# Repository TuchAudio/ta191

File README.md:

# ta191
Low Noise, improved Moving-Coil Phono Pre-Amp

## Purpose
An optional _previous_ stage for **MM Phono preamps** like [TuchAudio 101b](../../../ta101b), allowing the use of **Moving Coil** cartridges. _With suitable wiring_ it could be used with other preamps as well, like the [103](../../../ta103) board.

A _built-in relay_ allows the **same input connector** to be used with both **MC** (thru amplification) and **MM cartridges** (_bypassing_ it straight to the MM Phono stage)

## Design
The use of **four _common-base_ stages in parallel**  provides **low input impedance** (100 Ω) and **improved _signal-to-noise_ ratio** (by 6 dB).

_Symmetrical power supply_ thru **serial regulation** provides high PSRR.

## Specs
- **Power supply:** +/-9V, _symmetrical_ (just a few mA)
- **Gain:** x33 (+34 dB)
- **Input Sensitivity:** 0.11 mV over 100 Ω (for a 3.6 mV output, suitable for [TuchAudio 101b preamp](../../../ta101b) or [TuchAudio 103](../../../ta103))
- **Nominal Output level:** 3.6 mV over 110 kΩ (from a 0.11 mV input)
- **Output impedance:** 3.3 kΩ. _Lower load impedances are allowed, but diminished output level and impaired bass response are to be expected_.

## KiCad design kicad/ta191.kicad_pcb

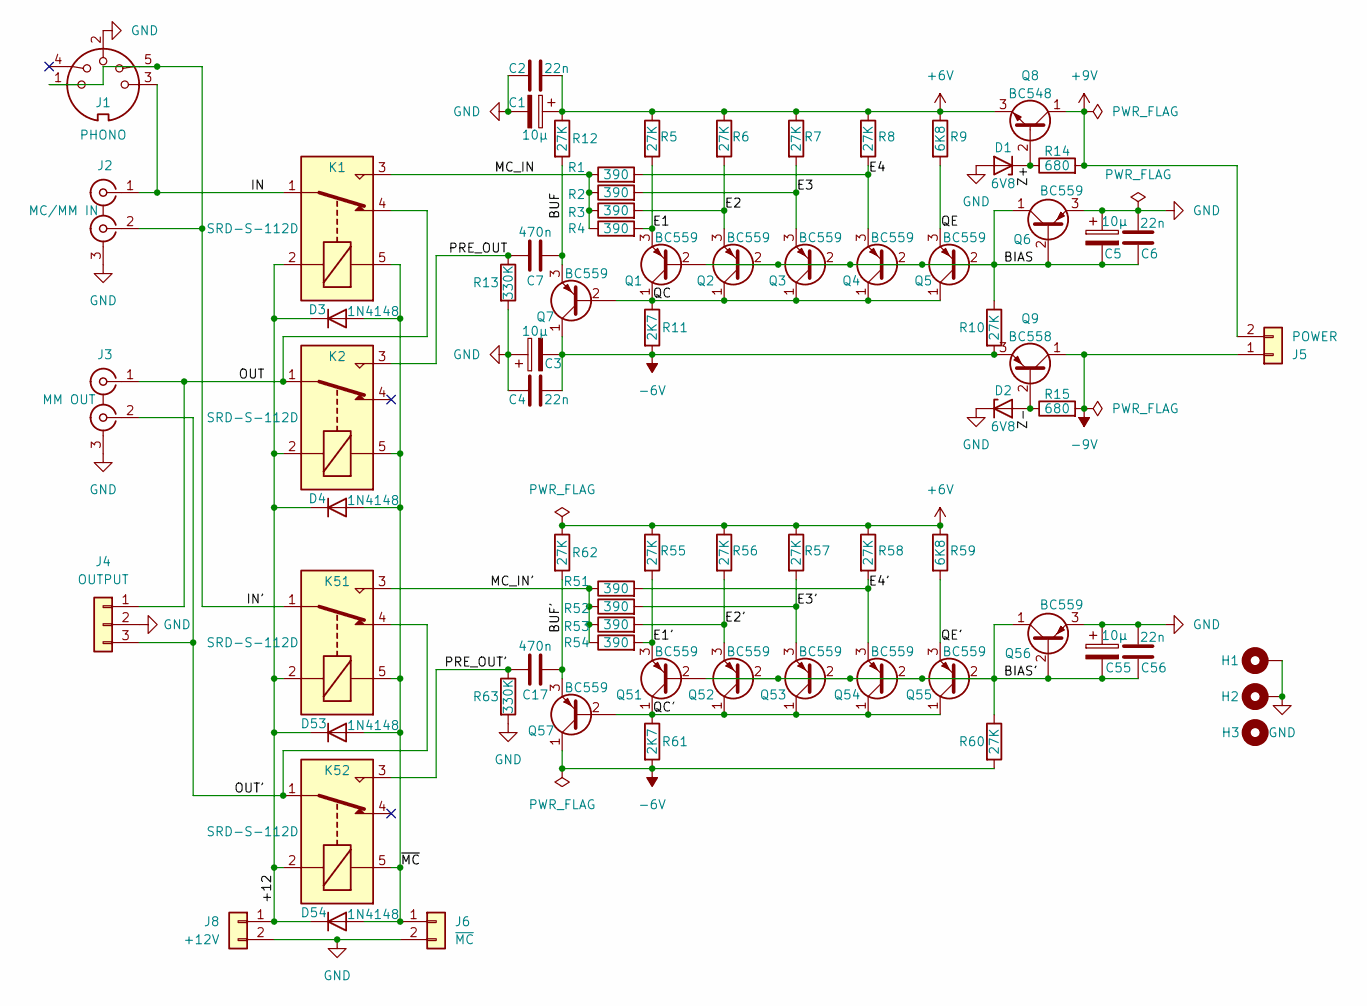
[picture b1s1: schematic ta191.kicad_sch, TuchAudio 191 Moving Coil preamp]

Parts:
C1, C3, C5, C55: 10µ; CP_Radial_D4.0mm_P1.50mm
C2, C4, C6, C56: 22n; C_Disc_D6.0mm_W2.5mm_P5.00mm
C7, C17: 470n; C_Rect_L7.2mm_W3.0mm_P5.00mm_FKS2_FKP2_MKS2_MKP2
D1, D2: 6V8; D_DO-35_SOD27_P7.62mm_Horizontal
D3, D4, D53, D54: 1N4148; D_DO-35_SOD27_P7.62mm_Horizontal
H1, H2: MountingHole_Pad; MountingHole_3.2mm_M3_DIN965_Pad
H3: MountingHole; MountingHole_3.2mm_M3
J1: PHONO; DIN 5-180deg
J2: MC/MM IN; 2xRCA_vertical
J3: MM OUT; 2xRCA_vertical
J4: OUTPUT; PinHeader_1x03_P2.54mm_Vertical
J5: POWER; PinHeader_1x02_P2.54mm_Vertical
J6: ~{MC}; PinHeader_1x02_P2.54mm_Vertical
J8: +12V; PinHeader_1x02_P2.54mm_Vertical
K1, K2, K51, K52: SRD-S-112D; Relay_SPDT_SANYOU_SRD_Series_Form_C
Q1, Q2, Q3, Q4, Q5, Q6, Q7, Q51, Q52, Q53, Q54, Q55, Q56, Q57: BC559; TO-92_Inline
Q8: BC548; TO-92_Inline
Q9: BC558; TO-92_Inline
R1, R2, R3, R4, R51, R52, R53, R54: 390; R_Axial_DIN0207_L6.3mm_D2.5mm_P10.16mm_Horizontal
R5, R6, R7, R8, R10, R12, R55, R56, R57, R58, R60, R62: 27K; R_Axial_DIN0207_L6.3mm_D2.5mm_P10.16mm_Horizontal
R9, R59: 6K8; R_Axial_DIN0207_L6.3mm_D2.5mm_P10.16mm_Horizontal
R11, R61: 2K7; R_Axial_DIN0207_L6.3mm_D2.5mm_P10.16mm_Horizontal
R13, R63: 330K; R_Axial_DIN0207_L6.3mm_D2.5mm_P10.16mm_Horizontal
R14, R15: 680; R_Axial_DIN0207_L6.3mm_D2.5mm_P10.16mm_Horizontal

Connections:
+6V: C1.1, C2.2, Q8.3 (E), R5.1, R6.1, R7.1, R8.1, R9.1, R12.1, R55.1, R56.1, R57.1, R58.1, R59.1, R62.1
+9V: J5.2, Q8.1 (C), R14.2
-6V: C3.2, C4.2, Q7.1 (C), Q9.3 (E), Q57.1 (C), R10.2, R11.2, R60.2, R61.2
-9V: J5.1, Q9.1 (C), R15.2
/+12: D3.1 (K), D4.1 (K), D53.1 (K), D54.1 (K), J8.1, K1.2, K2.2, K51.2, K52.2
/BIAS: C5.2, C6.2, Q1.2 (B), Q2.2 (B), Q3.2 (B), Q4.2 (B), Q5.2 (B), Q6.1 (C), Q6.2 (B), R10.1
/BIAS': C55.2, C56.2, Q51.2 (B), Q52.2 (B), Q53.2 (B), Q54.2 (B), Q55.2 (B), Q56.1 (C), Q56.2 (B), R60.1
/BUF: C7.2, Q7.3 (E), R12.2
/BUF': C17.2, Q57.3 (E), R62.2
/E1: Q1.3 (E), R4.2, R5.2
/E1': Q51.3 (E), R54.2, R55.2
/E2: Q2.3 (E), R3.2, R6.2
/E2': Q52.3 (E), R53.2, R56.2
/E3: Q3.3 (E), R2.2, R7.2
/E3': Q53.3 (E), R52.2, R57.2
/E4: Q4.3 (E), R1.2, R8.2
/E4': Q54.3 (E), R51.2, R58.2
/IN: J1.3, J2.1 (IN1), K1.1
/IN': J1.1, J1.5, J2.2 (IN2), K51.1
/MC_IN: K1.3, R1.1, R2.1, R3.1, R4.1
/MC_IN': K51.3, R51.1, R52.1, R53.1, R54.1
/OUT: J3.1 (IN1), J4.1, K1.4, K2.1
/OUT': J3.2 (IN2), J4.3, K51.4, K52.1
/PRE_OUT: C7.1, K2.3, R13.1
/PRE_OUT': C17.1, K52.3, R63.1
/QC: Q1.1 (C), Q2.1 (C), Q3.1 (C), Q4.1 (C), Q5.1 (C), Q7.2 (B), R11.1
/QC': Q51.1 (C), Q52.1 (C), Q53.1 (C), Q54.1 (C), Q55.1 (C), Q57.2 (B), R61.1
/QE: Q5.3 (E), R9.2
/QE': Q55.3 (E), R59.2
/Z+: D1.1 (K), Q8.2 (B), R14.1
/Z-: D2.2 (A), Q9.2 (B), R15.1
/~MC: D3.2 (A), D4.2 (A), D53.2 (A), D54.2 (A), J6.1, K1.5, K2.5, K51.5, K52.5
GND: C1.2, C2.1, C3.1, C4.1, C5.1, C6.1, C55.1, C56.1, D1.2 (A), D2.1 (K), H1.1, H2.1, J1.2, J2.3 (EXT), J3.3 (EXT), J4.2, J6.2, J8.2, Q6.3 (E), Q56.3 (E), R13.2, R63.2

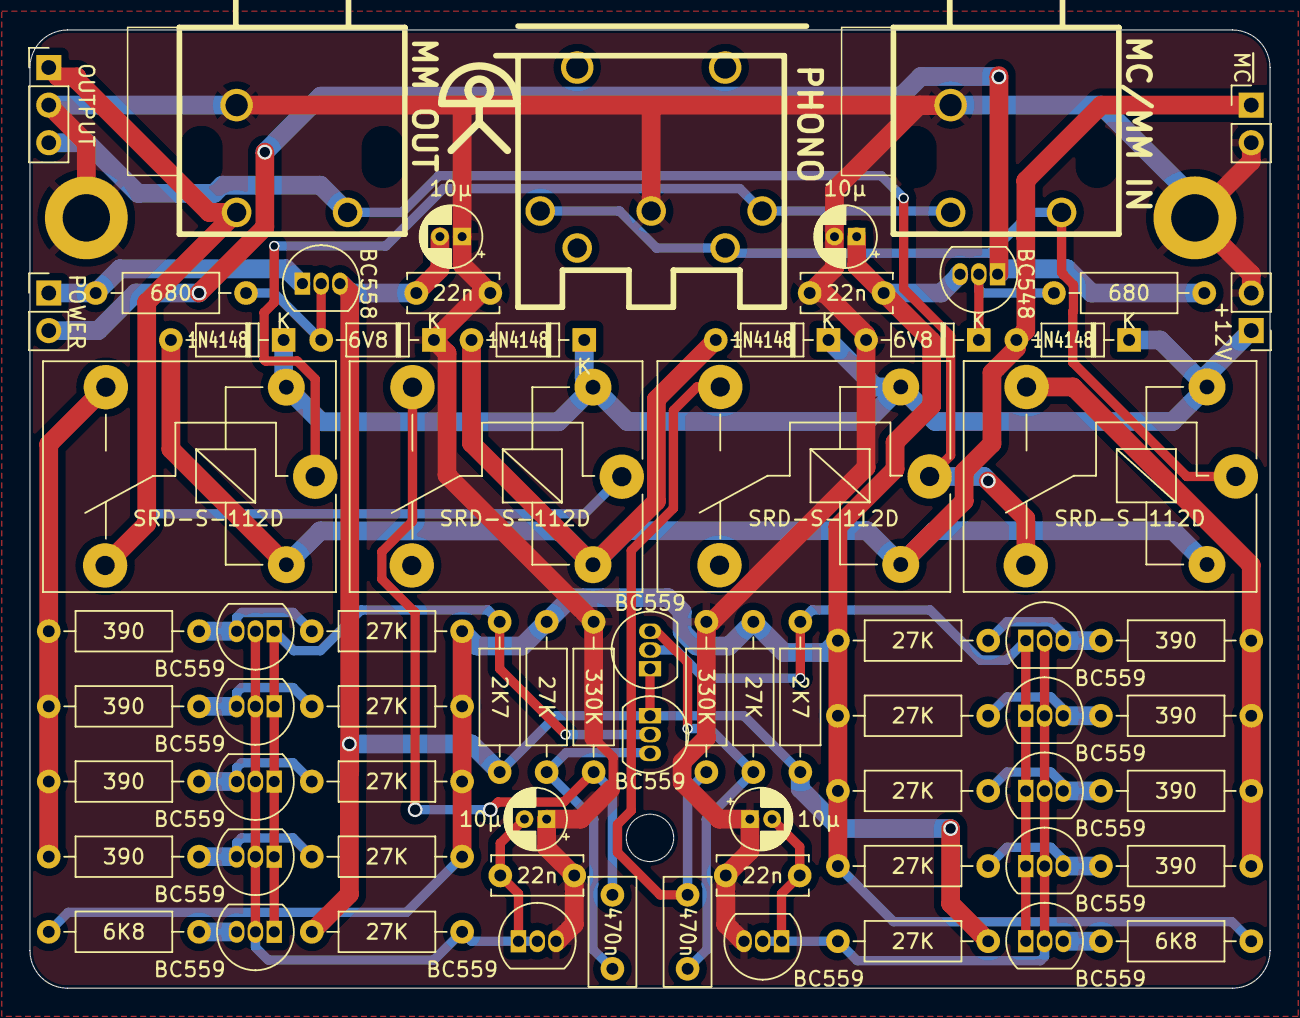
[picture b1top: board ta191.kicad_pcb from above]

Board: 2 copper layers, 83.8 x 64.8 mm, 74 parts (0 on the bottom side), 33 nets.

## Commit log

2025-11-08 add KiCAD files
2025-11-12 Add purpose section to README
    Added purpose section explaining the functionality of the preamp.
2025-11-24 links, design and temporary specs
2025-11-29 fix mounting holes
